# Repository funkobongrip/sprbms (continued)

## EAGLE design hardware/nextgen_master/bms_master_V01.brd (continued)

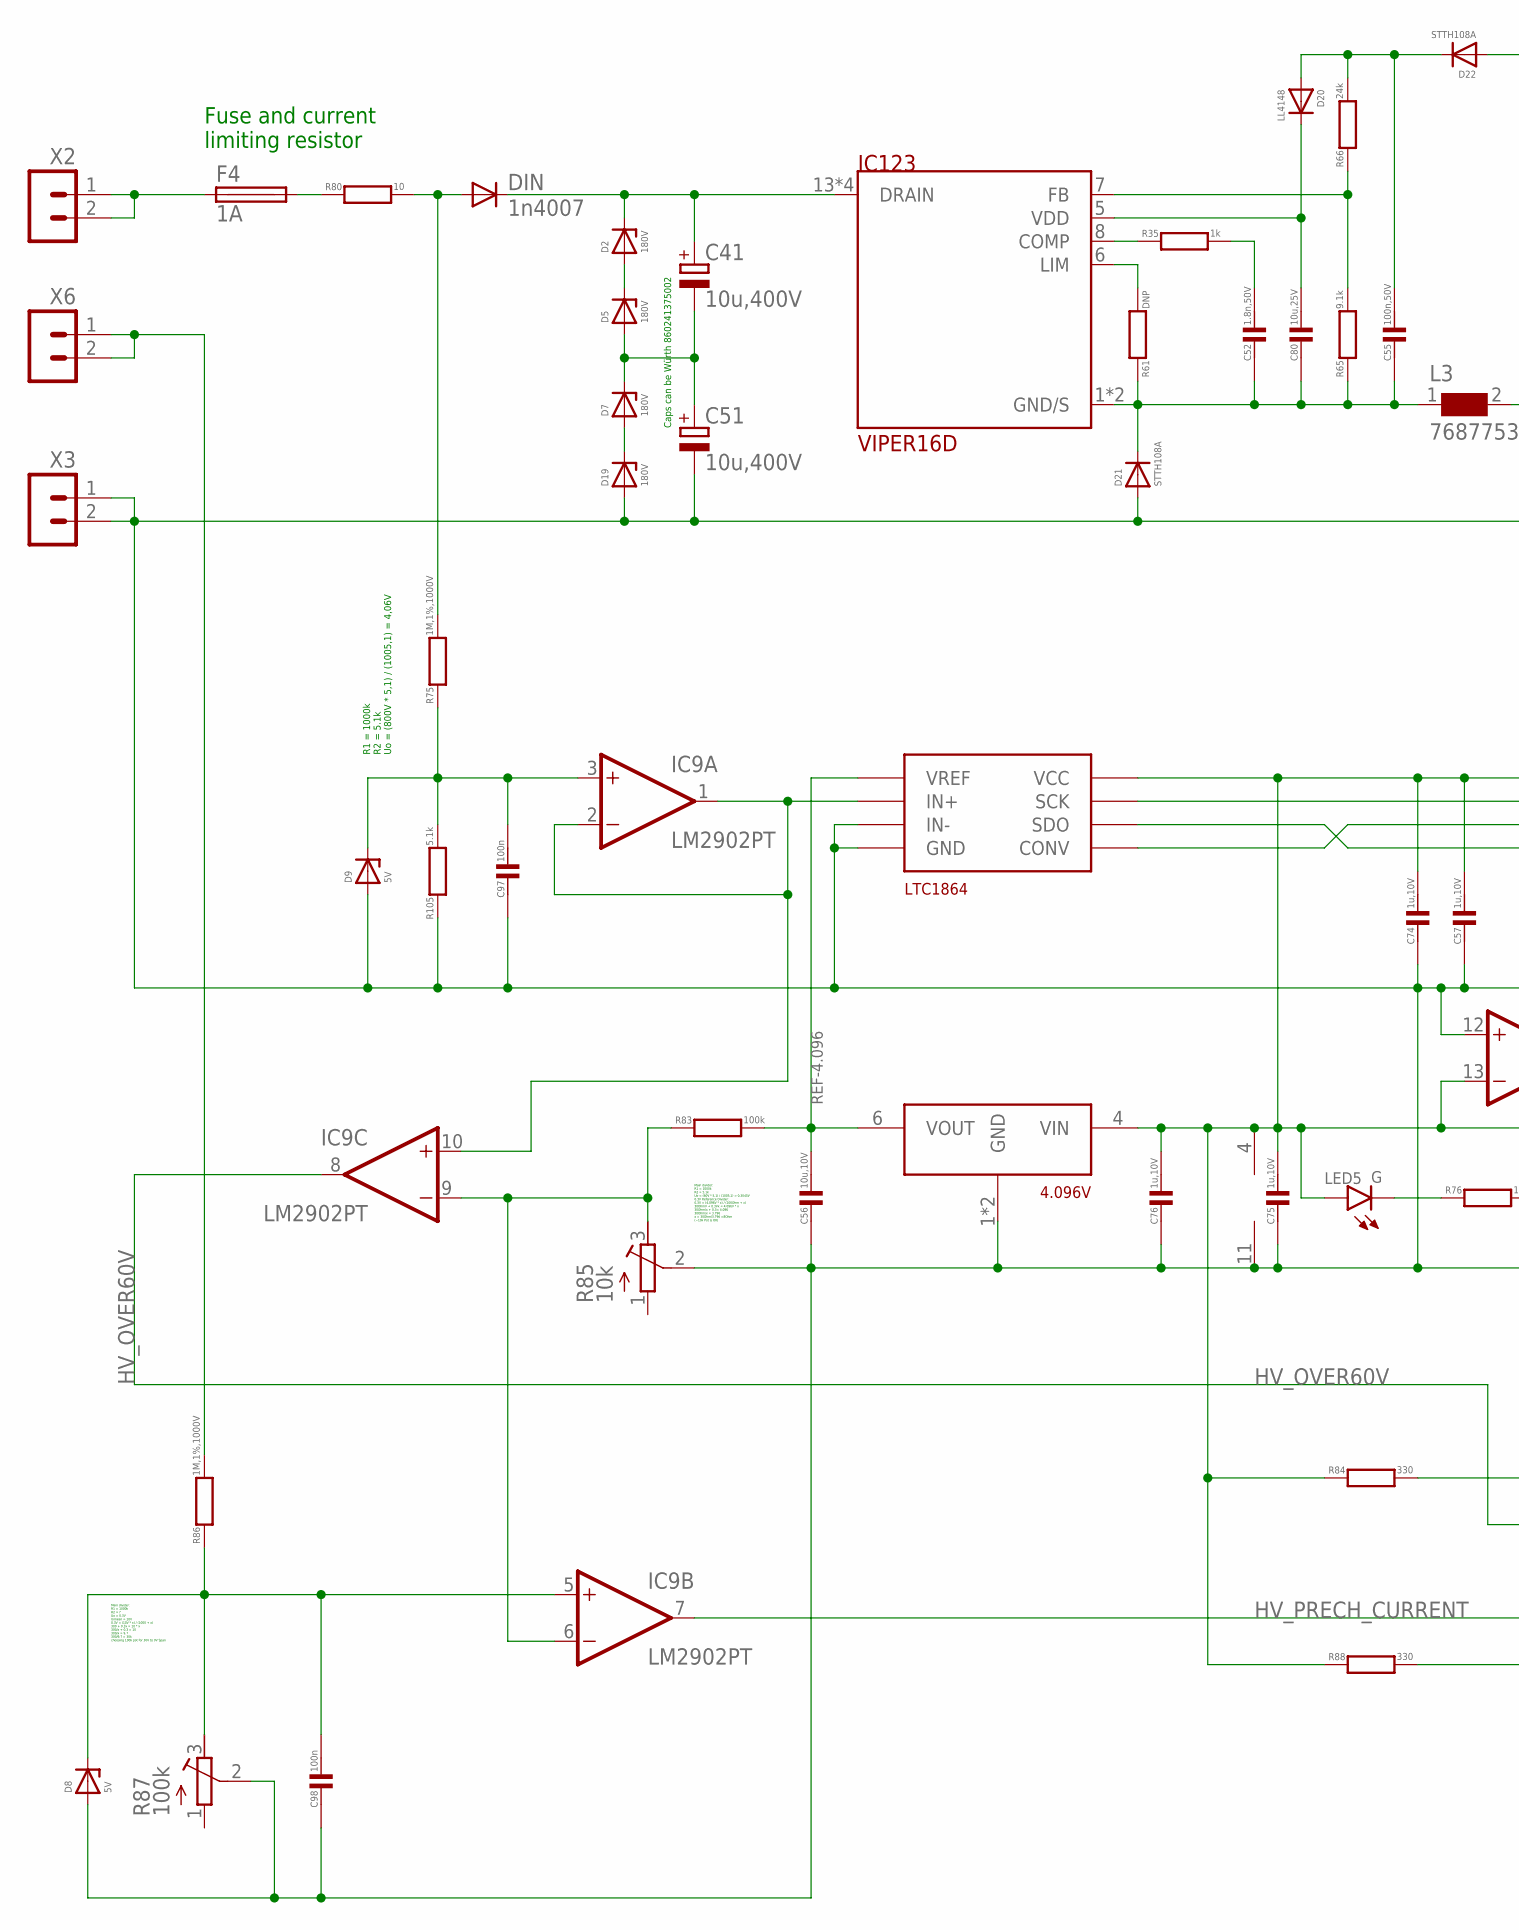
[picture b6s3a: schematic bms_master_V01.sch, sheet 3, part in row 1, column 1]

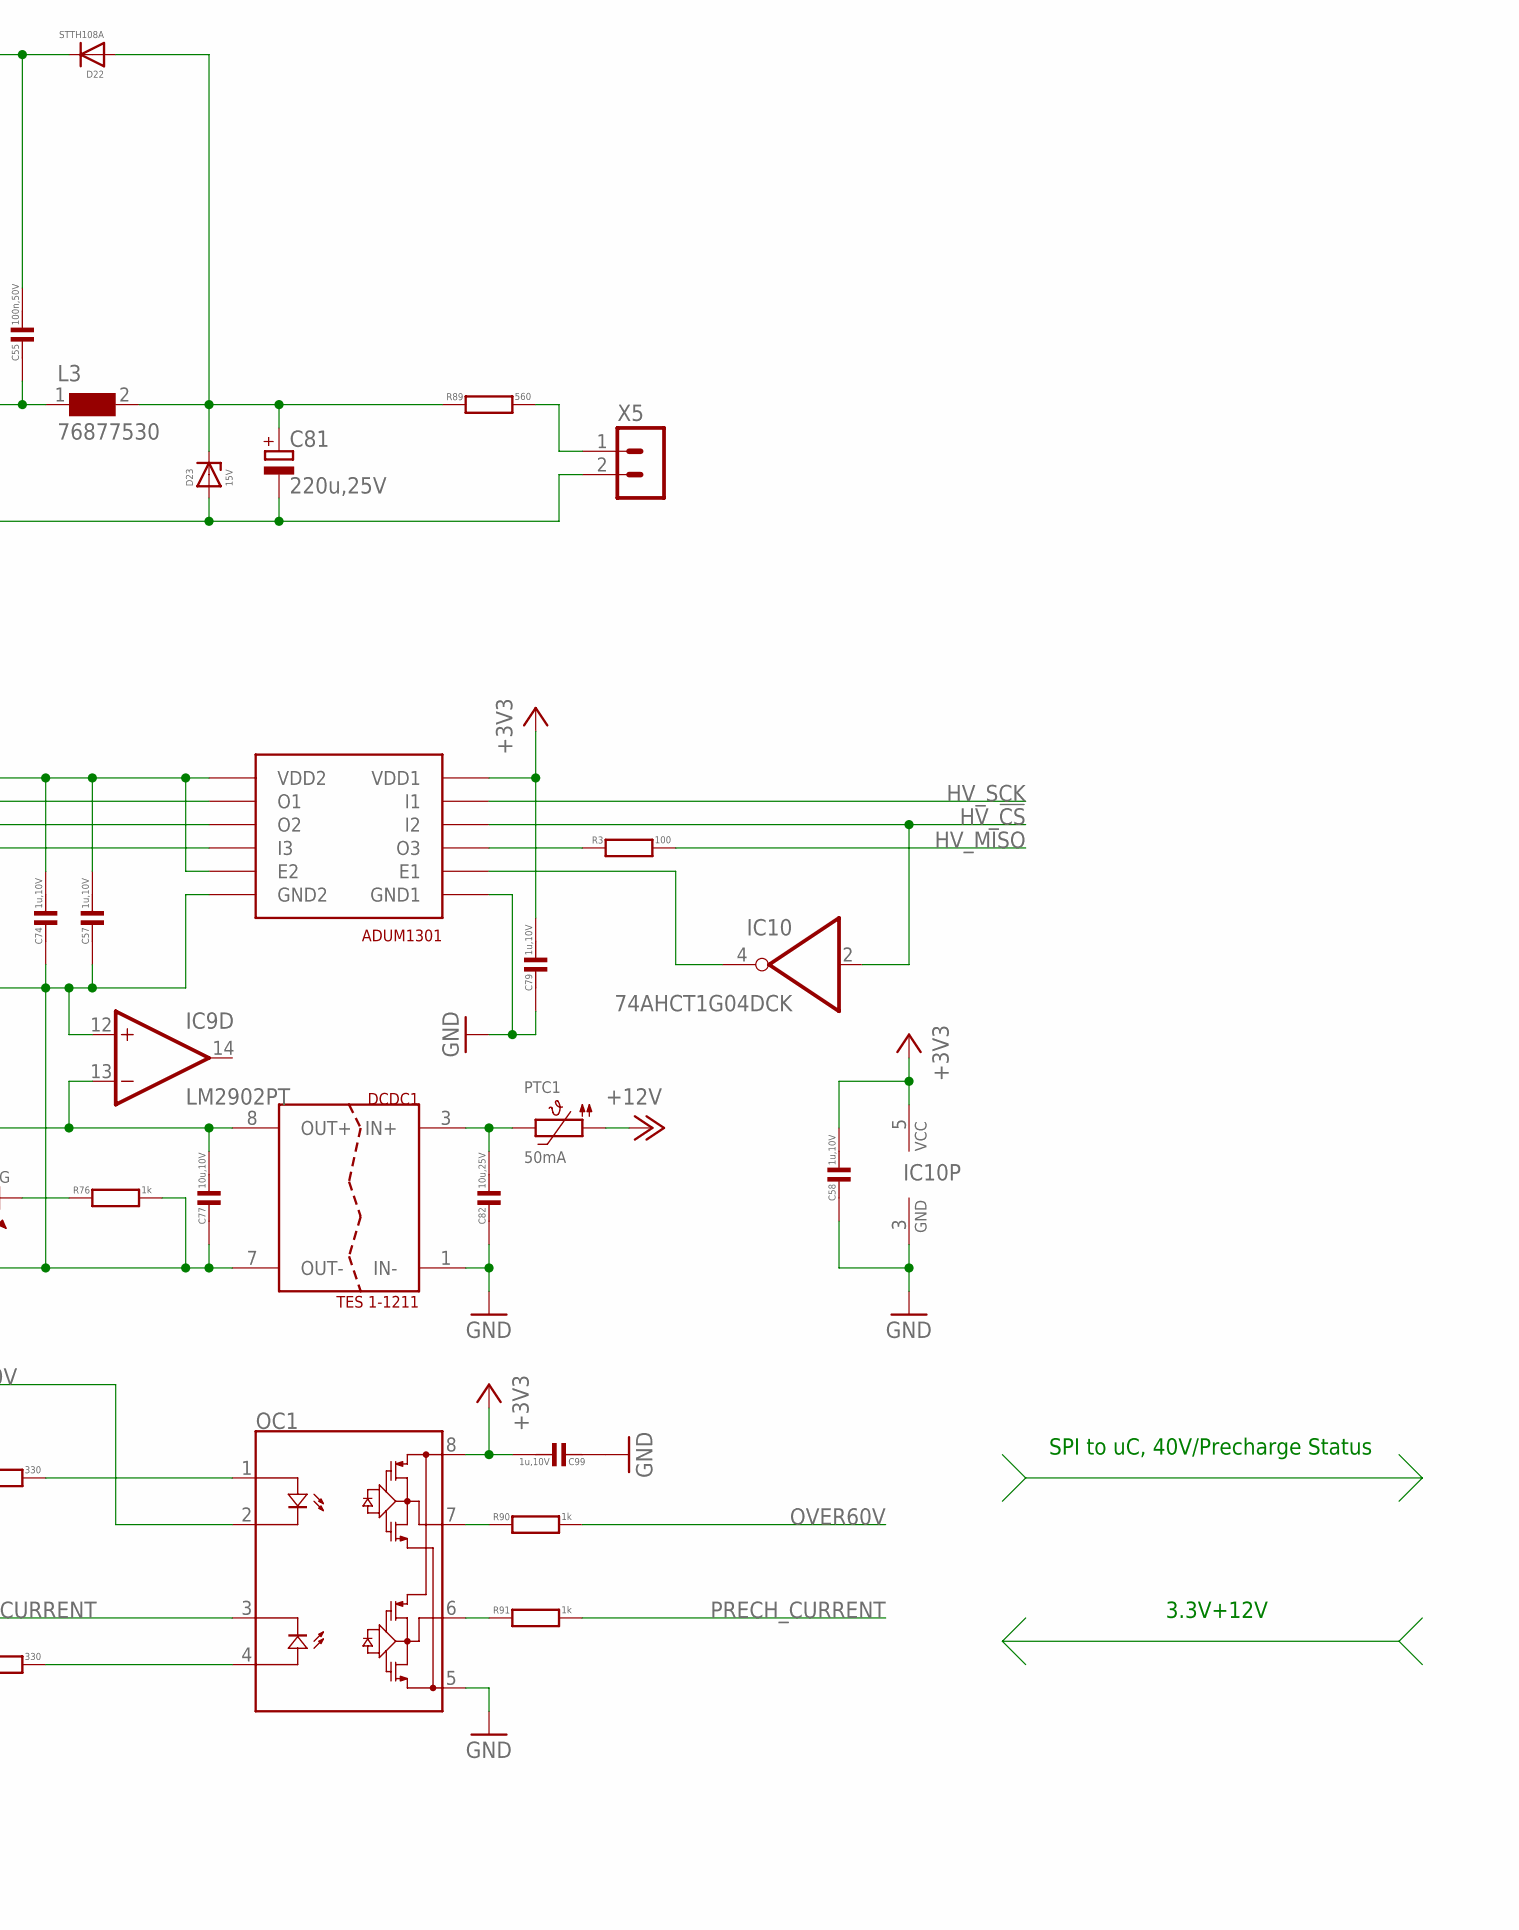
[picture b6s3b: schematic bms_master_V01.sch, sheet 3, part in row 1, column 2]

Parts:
C41, C51: 10u,400V; E5-10,5
C52: 1.8n,50V; C0603
C55: 100n,50V; C0603
C56, C77: 10u,10V; C0603
C57, C58, C74, C75, C76, C79, C99: 1u,10V; C0402
C80, C82: 10u,25V; C1210
C81: 220u,25V; E3,5-8
C97, C98: 100n; C0603
D2, D5, D7, D19: 180V; DO-214AC
D8, D9: 5V; SOD323-L
D20: LL4148; MINIMELF
D21, D22: STTH108A; DO-214AC
D23: 15V; DO-214AC
DCDC1: TES 1-1211; DCDC_SMD_TES1
DIN: 1n4007; DO-214AC
F4: 1A; LF485
IC9: LM2902PT; SSOP14
IC10: 74AHCT1G04DCK; SC70-5
IC123: VIPER16D; SO16
L3: 76877530; WE-PD2_7850
LED5: G; CHIPLED_0603
OC1: ACPL-K7X; SO-8-STRETCHED
PTC1: 50mA; PTC1210
R3: 100; R0402
R35: 1k; R0603
R61: DNP; R0603
R65: 9.1k; R0603
R66: 24k; R0603
R75, R86: 1M,1%,1000V; R2512
R76, R90, R91: 1k; R0402
R80: 10; R1206
R83: 100k; R0402
R84, R88: 330; R0402
R85: 10k; RTRIM3224W
R87: 100k; RTRIM3224W
R89: 560; R1206
R105: 5.1k; R1206
U$3: 4.096V; SOT23-6
U$20: LTC1864; MS8
U$22: ADUM1301; SO16WB
X2, X3, X5, X6: HEADER_POS2_43650-0212; 43650-0212

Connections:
+3V3: C58.1, C79.1, C99.1, IC10.5 (VCC), OC1.8, U$22.P$1 (VDD1); also elsewhere on the board
+12V: PTC1.P$1 (1); also elsewhere on the board
CHV_5V: C57.1, C74.1, C75.1, C76.1, C77.1, DCDC1.8 (OUT+), IC9.4 (V+), IC9.13 (-IN), LED5.A, R84.1, R88.1, U$3.4 (VIN), U$20.P$8 (VCC), U$22.P$10 (E2), U$22.P$16 (VDD2)
CHV_+: F4.1, X2.1, X2.2
CHV_+_FUSED: F4.2, R80.1
CHV_+_FUSEDR: DIN.A, R75.2, R80.2
CHV_CONV: U$20.P$5 (CONV), U$22.P$13 (O2)
CHV_GND: C51.-, C56.2, C57.2, C74.2, C75.2, C76.2, C77.2, C81.-, C97.2, C98.2, D8.A, D9.A, D19.A, D21.A, D23.A, DCDC1.7 (OUT-), IC9.11 (V-), IC9.12 (+IN), R76.2, R85.2 (S), R87.2 (S), R105.1, U$3.1 (GND), U$3.2 (GND), U$20.P$3 (IN-), U$20.P$4 (GND), U$22.P$9 (GND2), U$22.P$15 (GND2), X3.1, X3.2, X5.2
CHV_LEDC: LED5.C, R76.1
CHV_M: C97.1, D9.C, IC9.3 (+IN), R75.1, R105.2
CHV_M1: C98.1, D8.C, IC9.5 (+IN), R86.1, R87.3 (E)
CHV_MOP: IC9.1 (OUT), IC9.2 (-IN), IC9.10 (+IN), U$20.P$2 (IN+)
CHV_SCK: U$20.P$7 (SCK), U$22.P$14 (O1)
CHV_SDO: U$20.P$6 (SDO), U$22.P$12 (I3)
CLV_12V_TES1_FUSED: C82.1, DCDC1.3 (IN+), PTC1.P$2 (2)
GND: C58.2, C79.2, C82.2, C99.2, DCDC1.1 (IN-), IC10.3 (GND), OC1.5, U$22.P$2 (GND1), U$22.P$8 (GND1); also elsewhere on the board
HV_!CS: IC10.2 (I), U$22.P$4 (I2); also elsewhere on the board
HV_MISO: R3.2; also elsewhere on the board
HV_OVER60V: IC9.8 (OUT), OC1.2
HV_PRECH_CURRENT: IC9.7 (OUT), OC1.3
HV_SCK: U$22.P$3 (I1); also elsewhere on the board
unnamed: IC10.4 (O), U$22.P$7 (E1)
unnamed: R3.1, U$22.P$5 (O3)
unnamed: R86.2, X6.1, X6.2
unnamed: OC1.1, R84.2
unnamed: OC1.4, R88.2
OVER60V: R90.2; also elsewhere on the board
PRECH_CURRENT: R91.2; also elsewhere on the board
R!OVER40V: OC1.7, R90.1
R!PRECH_CURRENT: OC1.6, R91.1
REF0.3W: IC9.6 (-IN), IC9.9 (-IN), R83.1, R85.3 (E)
REF-4.096: C56.1, R83.2, U$3.6 (VOUT), U$20.P$1 (VREF)
VP+3/4: D7.A, D19.C
VP_12V: C81.+, D22.A, D23.C, L3.2, R89.1
VP_12VINT: C55.1, D20.A, D22.C, R66.2
VP_+: C41.+, D2.C, DIN.C, IC123.13 (DRAIN), IC123.14 (DRAIN), IC123.15 (DRAIN), IC123.16 (DRAIN)
VP_+1/3: D2.A, D5.C
VP_+/2: C41.-, C51.+, D5.A, D7.C
VP_COMP: IC123.8 (COMP), R35.1
VP_COMPM: C52.1, R35.2
VP_FB: IC123.7 (FB), R65.2, R66.1
VP_LED: R89.2, X5.1
VP_LIM: IC123.6 (LIM), R61.2
VP_S: C52.2, C55.2, C80.2, D21.C, IC123.1 (GND/S), IC123.2 (GND/S), L3.1, R61.1, R65.1
VP_VDD: C80.1, D20.C, IC123.5 (VDD)

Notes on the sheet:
Fuse and current limiting resistor
Caps can be Würth 860241375002
R1 = 1000k R2 = 5.1k Uo = (800V * 5,1) / (1005,1) = 4,06V
SPI to uC, 40V/Precharge Status
3.3V+12V
Main divider: R1 = 1000k R2 = 5.1k Uo = (60V * 5,1) / (1005,1) = 0.3045V 0.3V Reference Divider: 0.3V = (4.096V * x) / (100Ohm + x) 30OhmV + 0.3Vx = 4.096V * x 30Ohm/x + 0.3= 4.096 30Ohm/x = 3.796 x = 30Ohm/3.796 =8Ohm (~10k Pot is OK)
Main divider: R1 = 1000k R2 = ? Uo = 0.3V Uimean = 10V 0.3V = (10V * x) / (1000 + x) 300 + 0.3x = 10 * x 300/x + 0.3 = 10 300/x = 9.7 300/9.7 = 30k choosing 100k pot for 30V to 0V Span

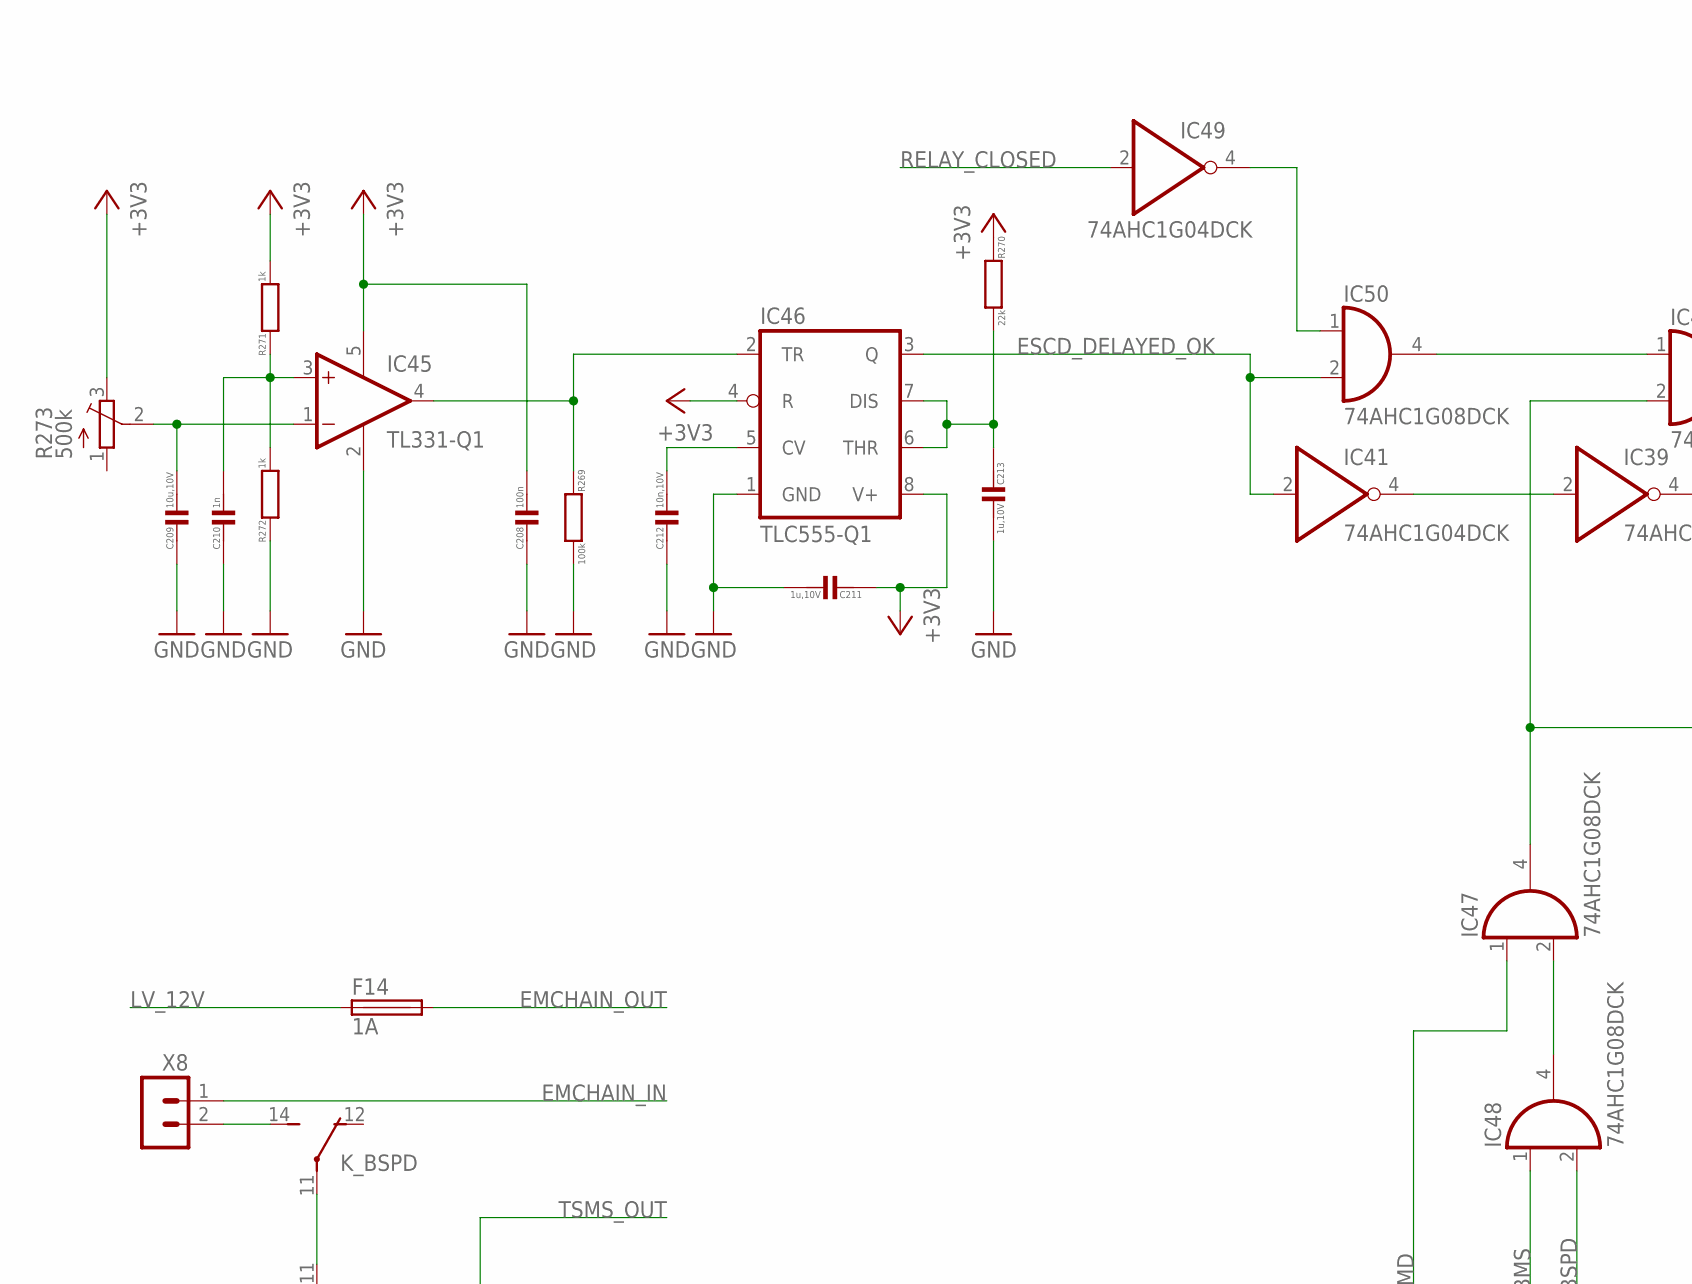
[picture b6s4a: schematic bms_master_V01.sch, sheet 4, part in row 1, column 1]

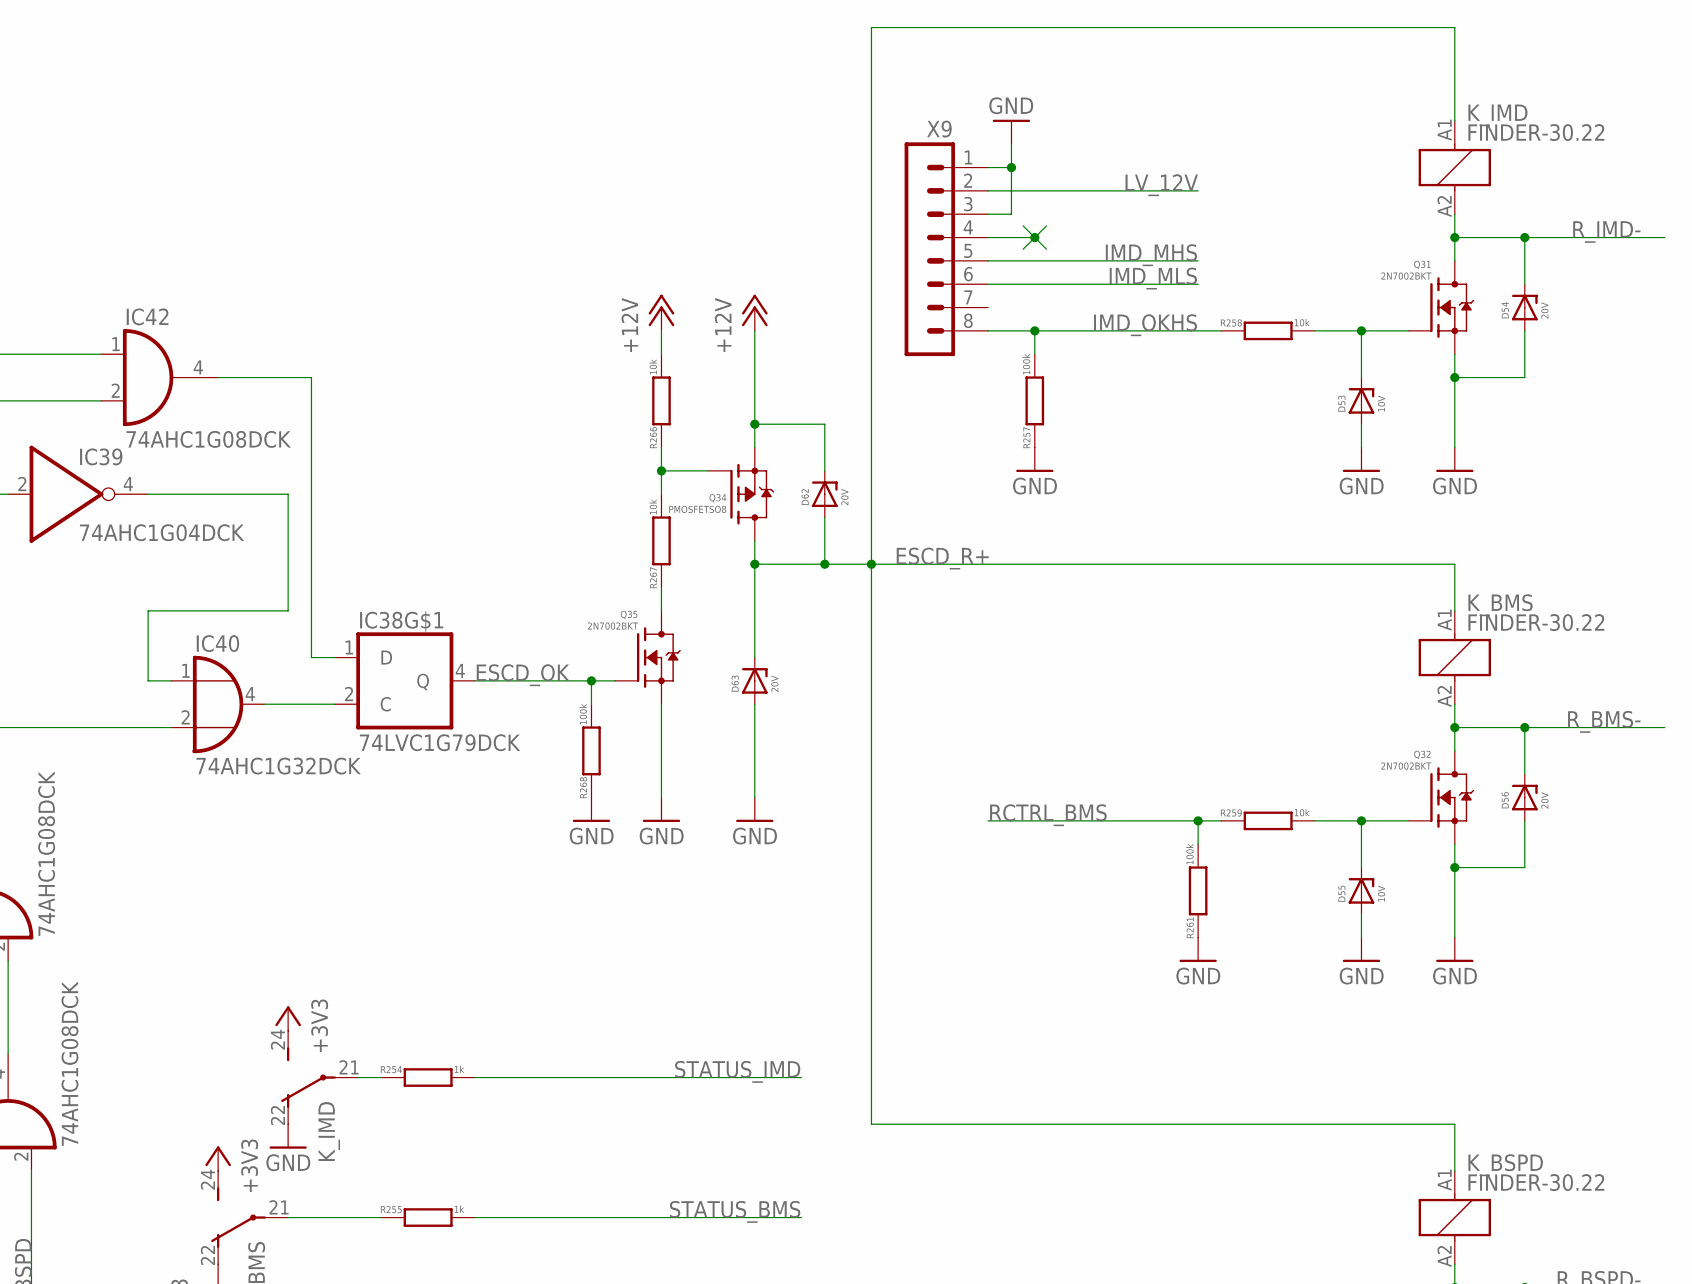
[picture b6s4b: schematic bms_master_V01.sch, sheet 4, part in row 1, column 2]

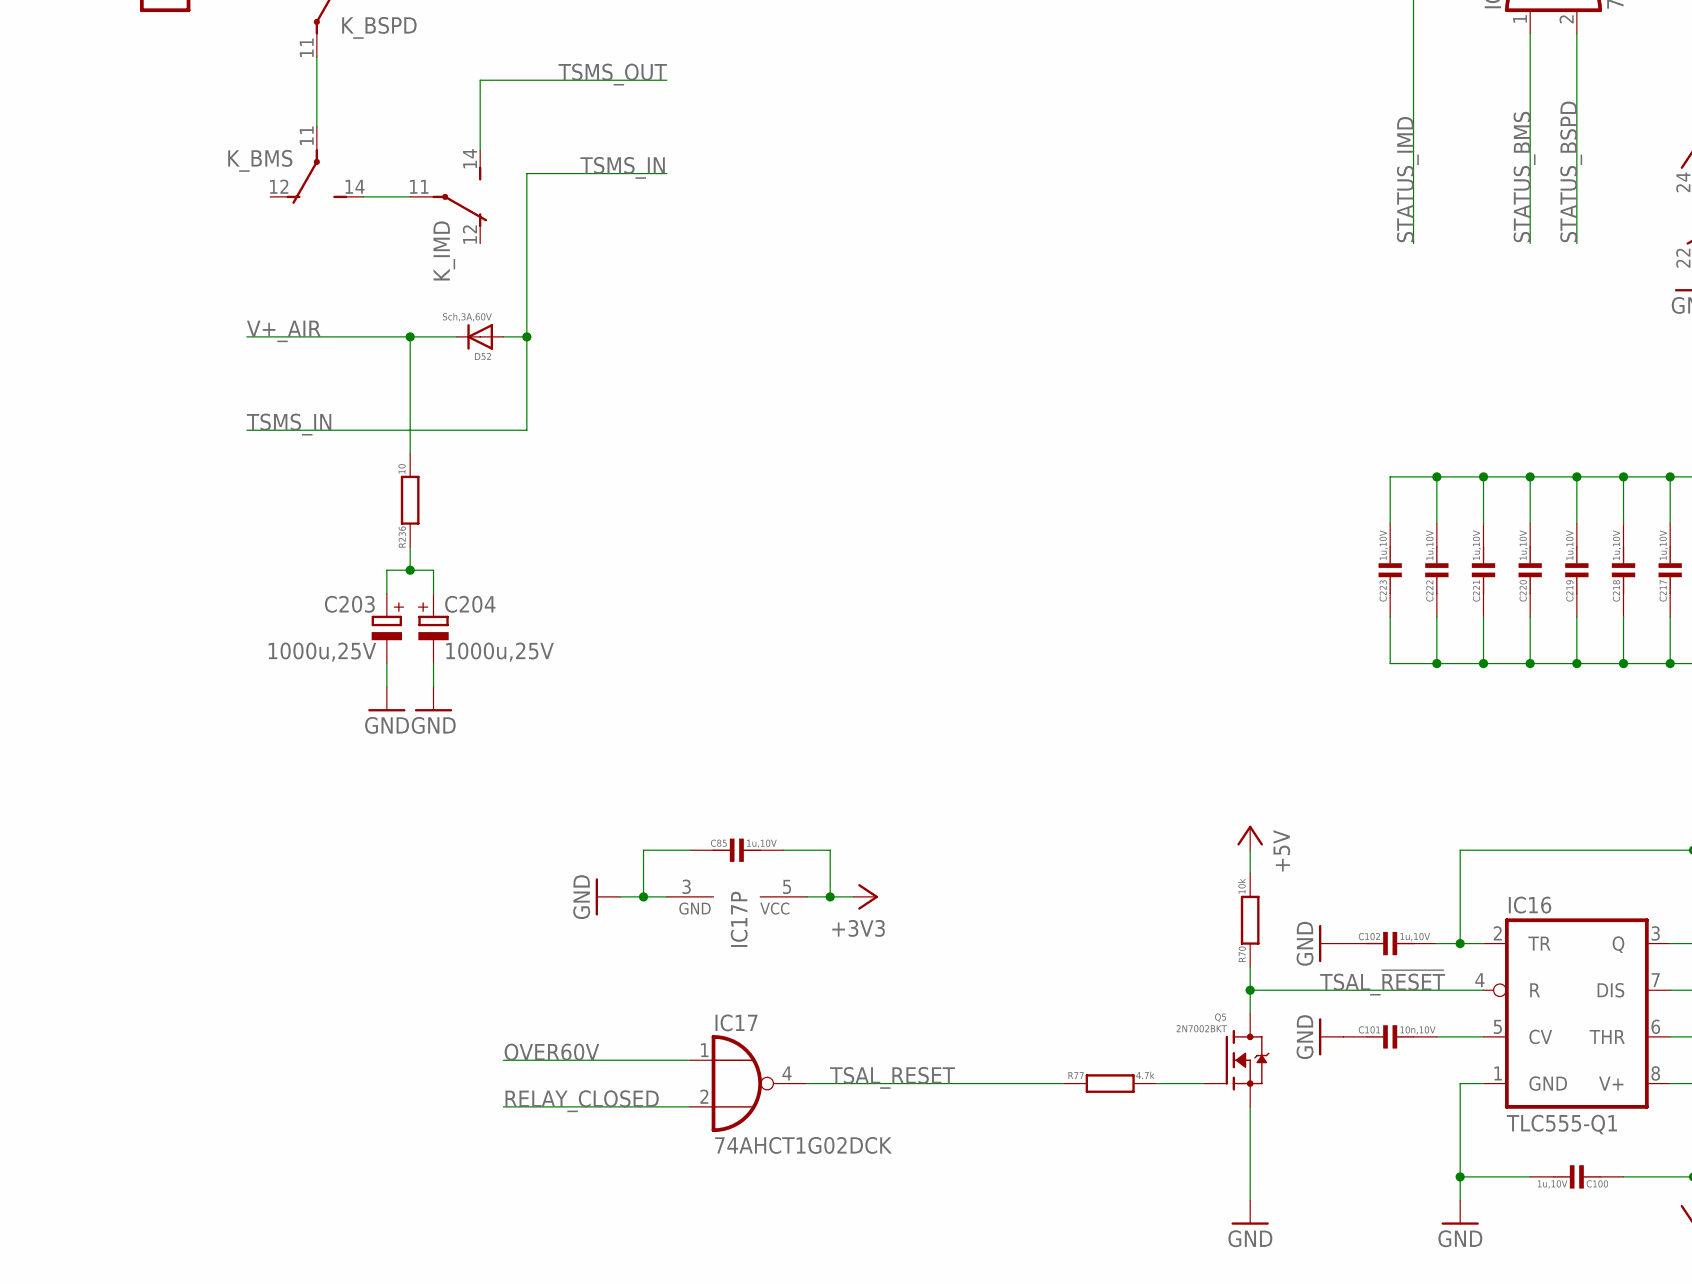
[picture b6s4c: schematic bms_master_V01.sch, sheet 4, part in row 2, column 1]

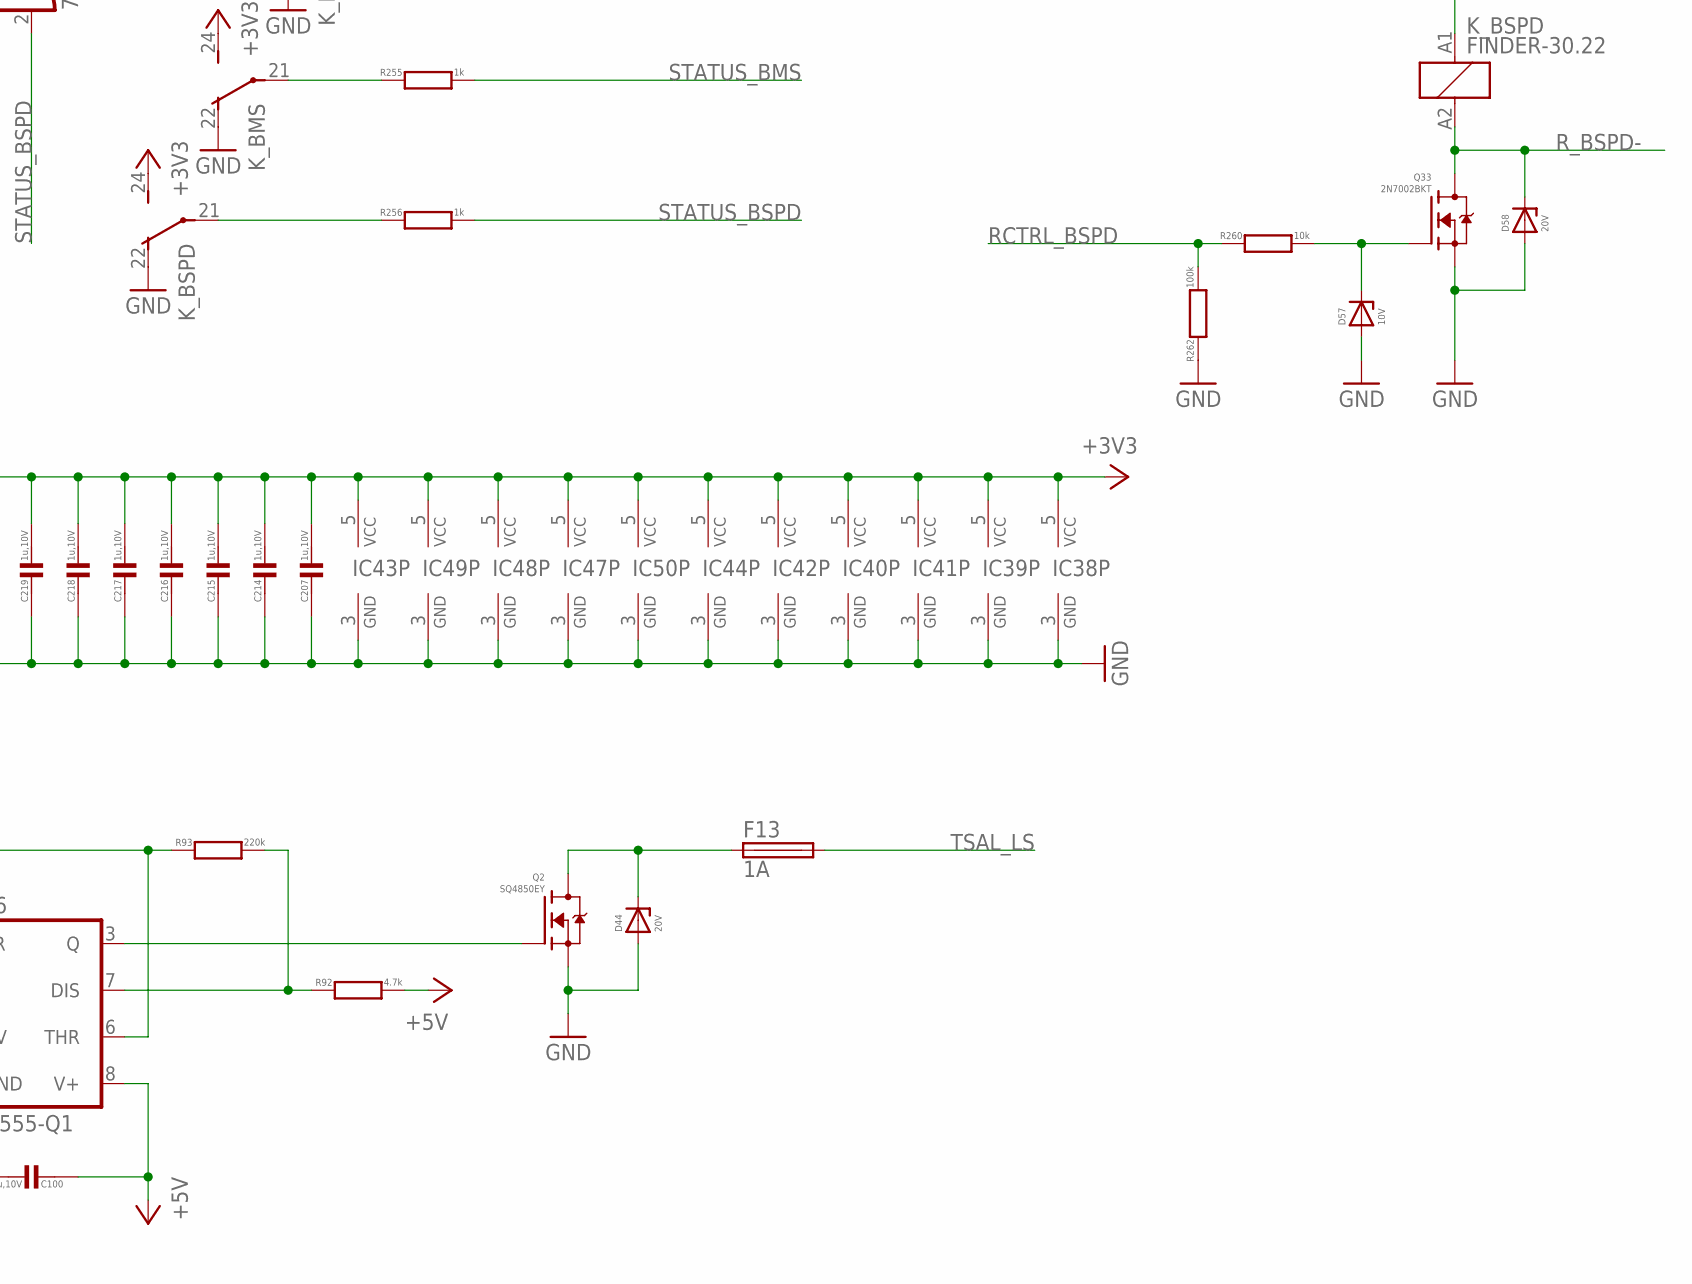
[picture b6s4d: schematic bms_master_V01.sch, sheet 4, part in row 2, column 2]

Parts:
C85, C100, C102, C207, C211, C213, C214, C215, C216, C217, C218, C219, C220, C221, C222, C223: 1u,10V; C0402
C101, C212: 10n,10V; C0402
C203, C204: 1000u,25V; E5-13
C208: 100n; C0402
C209: 10u,10V; C0603
C210: 1n; C0402
D44, D54, D56, D58, D62, D63: 20V; DO-214AC
D52: Sch,3A,60V; DO-214AC
D53, D55, D57: 10V; SOD323-L
F13, F14: 1A; LITTLEFUSE_17867640001
IC16, IC46: TLC555-Q1; SO08
IC17: 74AHCT1G02DCK; SC70-5
IC38: 74LVC1G79DCK; SC70-5
IC39, IC41, IC49: 74AHC1G04DCK; SC70-5
IC40, IC43: 74AHC1G32DCK; SC70-5
IC42, IC47, IC48, IC50: 74AHC1G08DCK; SC70-5
IC44: 74AHC1G02DCK; SC70-5
IC45: TL331-Q1; DBV-R-PDSO-G5
K_BMS: FINDER-30.22
K_BSPD: FINDER-30.22
K_IMD: FINDER-30.22
Q2: SQ4850EY; SO-8
Q5, Q31, Q32, Q33, Q35: 2N7002BKT; SOT416
Q34: PMOSFETSO8; SO-8
R70, R258, R259, R260, R266, R267: 10k; R0402
R77, R92: 4.7k; R0402
R93: 220k; R0402
R236: 10; R1206
R254, R255, R256, R271, R272: 1k; R0402
R257, R261, R262, R268, R269: 100k; R0402
R270: 22k; R0402
R273: 500k; 3223W
X8: HEADER_POS2_43650-0212; 43650-0212
X9: HEADER_POS8_43650-0812; 43650-0812

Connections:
8VREF1: C209.1, IC45.1 (-IN), R273.2 (S)
+3V3: C85.1, C207.1, C208.1, C211.2, C214.1, C215.1, C216.1, C217.1, C218.1, C219.1, C220.1, C221.1, C222.1, C223.1, IC17.5 (VCC), IC38.5 (VCC), IC39.5 (VCC), IC40.5 (VCC), IC41.5 (VCC), IC42.5 (VCC), IC43.5 (VCC), IC44.5 (VCC), IC45.5 (V+), IC46.4 (R), IC46.8 (V+), IC47.5 (VCC), IC48.5 (VCC), IC49.5 (VCC), IC50.5 (VCC), K_BMS.24 (S), K_BSPD.24 (S), K_IMD.24 (S), R270.1, R271.2, R273.3 (E); also elsewhere on the board
+12V: D62.C, Q34.1 (S), Q34.2 (S), Q34.3 (S), R266.2; also elsewhere on the board
CAR+5V: C100.2, IC16.8 (V+), R70.2, R92.2
EMCHAIN_IN: X8.1
EMCHAIN_OUT: F14.2
ESCD_DELAYED_OK: IC41.2 (I), IC46.3 (Q), IC50.2 (I1)
ESCD_OK: IC38.4 (Q), Q35.1 (G), R268.2
ESCD_R+: D62.A, D63.C, K_BMS.A1 (1), K_BSPD.A1 (1), K_IMD.A1 (1), Q34.5 (D), Q34.6 (D), Q34.7 (D), Q34.8 (D)
GND: C85.2, C100.1, C101.2, C102.2, C203.-, C204.-, C207.2, C208.2, C209.2, C210.2, C211.1, C212.2, C213.1, C214.2, C215.2, C216.2, C217.2, C218.2, C219.2, C220.2, C221.2, C222.2, C223.2, D44.A, D53.A, D54.A, D55.A, D56.A, D57.A, D58.A, D63.A, IC16.1 (GND), IC17.3 (GND), IC38.3 (GND), IC39.3 (GND), IC40.3 (GND), IC41.3 (GND), IC42.3 (GND), IC43.3 (GND), IC44.3 (GND), IC45.2 (GND), IC46.1 (GND), IC47.3 (GND), IC48.3 (GND), IC49.3 (GND), IC50.3 (GND), K_BMS.22 (O), K_BSPD.22 (O), K_IMD.22 (O), Q2.1 (S), Q2.2 (S), Q2.3 (S), Q5.2 (S), Q31.2 (S), Q32.2 (S), Q33.2 (S), Q35.2 (S), R257.1, R261.1, R262.1, R268.1, R269.2, R272.1, X9.1, X9.3; also elsewhere on the board
IMD_MHS: X9.5
IMD_MLS: X9.6
IMD_OKHS: R257.2, R258.1, X9.8
LV_12V: F14.1, X9.2; also elsewhere on the board
unnamed: IC16.3 (Q), Q2.4 (G)
unnamed: K_BSPD.14 (S), X8.2
unnamed: K_BMS.11, K_BSPD.11
unnamed: K_BMS.14 (S), K_IMD.11
unnamed: C203.+, C204.+, R236.1
unnamed: K_BSPD.21, R256.1
unnamed: K_BMS.21, R255.1
unnamed: K_IMD.21, R254.1
unnamed: D53.C, Q31.1 (G), R258.2
unnamed: D55.C, Q32.1 (G), R259.2
unnamed: D57.C, Q33.1 (G), R260.2
unnamed: Q34.4 (G), R266.1, R267.2
unnamed: Q35.3 (D), R267.1
unnamed: IC38.2 (C), IC40.4 (O)
unnamed: IC39.4 (O), IC40.1 (I0)
unnamed: IC39.2 (I), IC41.4 (O)
unnamed: IC38.1 (D), IC42.4 (O)
unnamed: IC40.2 (I1), IC42.2 (I1), IC47.4 (O)
unnamed: IC47.2 (I1), IC48.4 (O)
unnamed: C210.1, IC45.3 (+IN), R271.1, R272.2
unnamed: IC45.4 (OUT), IC46.2 (TR), R269.1
unnamed: C213.2, IC46.6 (THR), IC46.7 (DIS), R270.2
unnamed: IC42.1 (I0), IC50.4 (O)
unnamed: IC49.4 (O), IC50.1 (I0)
OVER60V: IC17.1 (I0); also elsewhere on the board
RCTRL_BMS: R259.1, R261.2
RCTRL_BSPD: R260.1, R262.2
RELAY_CLOSED: IC17.2 (I1), IC49.2 (I); also elsewhere on the board
R_BMS-: D56.C, K_BMS.A2 (2), Q32.3 (D)
R_BSPD-: D58.C, K_BSPD.A2 (2), Q33.3 (D)
R_IMD-: D54.C, K_IMD.A2 (2), Q31.3 (D)
STATUS_BMS: IC48.1 (I0), R255.2; also elsewhere on the board
STATUS_BSPD: IC48.2 (I1), R256.2; also elsewhere on the board
STATUS_IMD: IC47.1 (I0), R254.2; also elsewhere on the board
TSAL_!RESET: IC16.4 (R), Q5.3 (D), R70.1
TSAL_CV: C101.1, IC16.5 (CV)
TSAL_CV1: C212.1, IC46.5 (CV)
TSAL_DIS: IC16.7 (DIS), R92.1, R93.2
TSAL_DRAIN: D44.C, F13.1, Q2.5 (D), Q2.6 (D), Q2.7 (D), Q2.8 (D)
TSAL_ENG: Q5.1 (G), R77.2
TSAL_LS: F13.2
TSAL_RESET: IC17.4 (O), R77.1
TSAL_TR: C102.1, IC16.2 (TR), IC16.6 (THR), R93.1
TSMS_IN: D52.A
TSMS_OUT: K_IMD.14 (S)
V+_AIR: D52.C, R236.2
